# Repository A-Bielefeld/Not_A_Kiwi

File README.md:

# Not_A_Kiwi

This is an old begineer project, this electronics shouldn't be replicated or used for may reasons. It stands here as an archive to remind myself of how my very first project turned out!

Not A Kiwi is an Open-Source, fully 3D printed modular robot controlled by a custom PCB. Its aims are to be an educational platform for engineering students and an entry in the 2019 Coupe de France de Robotique for the Robotics Assocations of Télécom Physique Strasbourg as a secondary robot.

This robot is meant for anyone seeking to have a fun and looking for an open robotics plateform to learn and expand on. The only tool needed to build one is a 3D printer, as the PCB can be bought online or provided by me (soldered or not).

## Features
- Based on a standard ATMega32, the board is arduino compatible (tested).
- Many headers and an integrated breadboard to test out new ideas and add sensors.
- Very easy to print, no complex parts.
- Modular 3D printed structure makes it easy to add any kind of sensor or effector.
- ESP01 socket (UART or I2C communication with the AVR) for IoT applications.

## Hardware
The hardware is the most developped part of this project as the code is still being written.

### BOM
- 4 Nema17 stepper motors (38mm)
- 4 DRV8825 stepper motor driver carriers (or A4988-Pinout-Compatible)
- 5V Pololu Regulator (D24V5F5, but I intend to replace them with a simpler/cheaper solution)
- 3.3V Pololu regulator (D24V5F3)
- ESP01 (not required)
- 12V LiPo battery (but any 12V to 36V battery will work fine)
- Not A Kiwi Board (Detailed below)
- Small Breadboard
- 30mm 0.15A fan
- 3D printed structure

#### Not A Kiwi Board

The board is a simple Atmega32 based board that includes 4 stepper motor driver carriers sockets as well as support for an ESP01 chip, communicating over either UART or I2C depending on a choice of jumpers. The BOM is rather small, as the board is meant to be programmed through ICSP. It is easily possible to send the BOM and Gerber files to a PCB production service to obtain one, although I can also provide fully soldered and tested ones for a fee (Europe only).

#### PCB BOM
The board uses a majority of SMD components, all 1206 except the AVR smoothing capacitor and a zener diode.

Most of these components can be soldered by hand, although it is advised to use solder paste and a reflow oven (a simple and inexpensive toaster oven is enough for this purpose).

Full BOM files will be provided in the repository, in a format compatible with most PCB manufacturers. 
An article explaining the choices behind the parts, and possible alternatives will be available on the wiki.

#### 3D printed structure

  The robot uses a simple 3D printed structure composed of 12 parts, it takes approximately 12 hours to print, not counting in the 3D printed omniwheels, but it would be much better to use bought ones, albeit more expensive (3D printed wheels have a negligeable cost, but perform more poorly, several design will be tested and offered here).
  
  The CAD files provided are Fusion 360 parametric files and therefore should also be compatible with Autodesk Inventor and SolidWorks (tested). If you just wish to print the robot, .STL files are also provided. The Kit also uses M3 screws and nuts, it is very quick and easy to assemble (less than an hour).

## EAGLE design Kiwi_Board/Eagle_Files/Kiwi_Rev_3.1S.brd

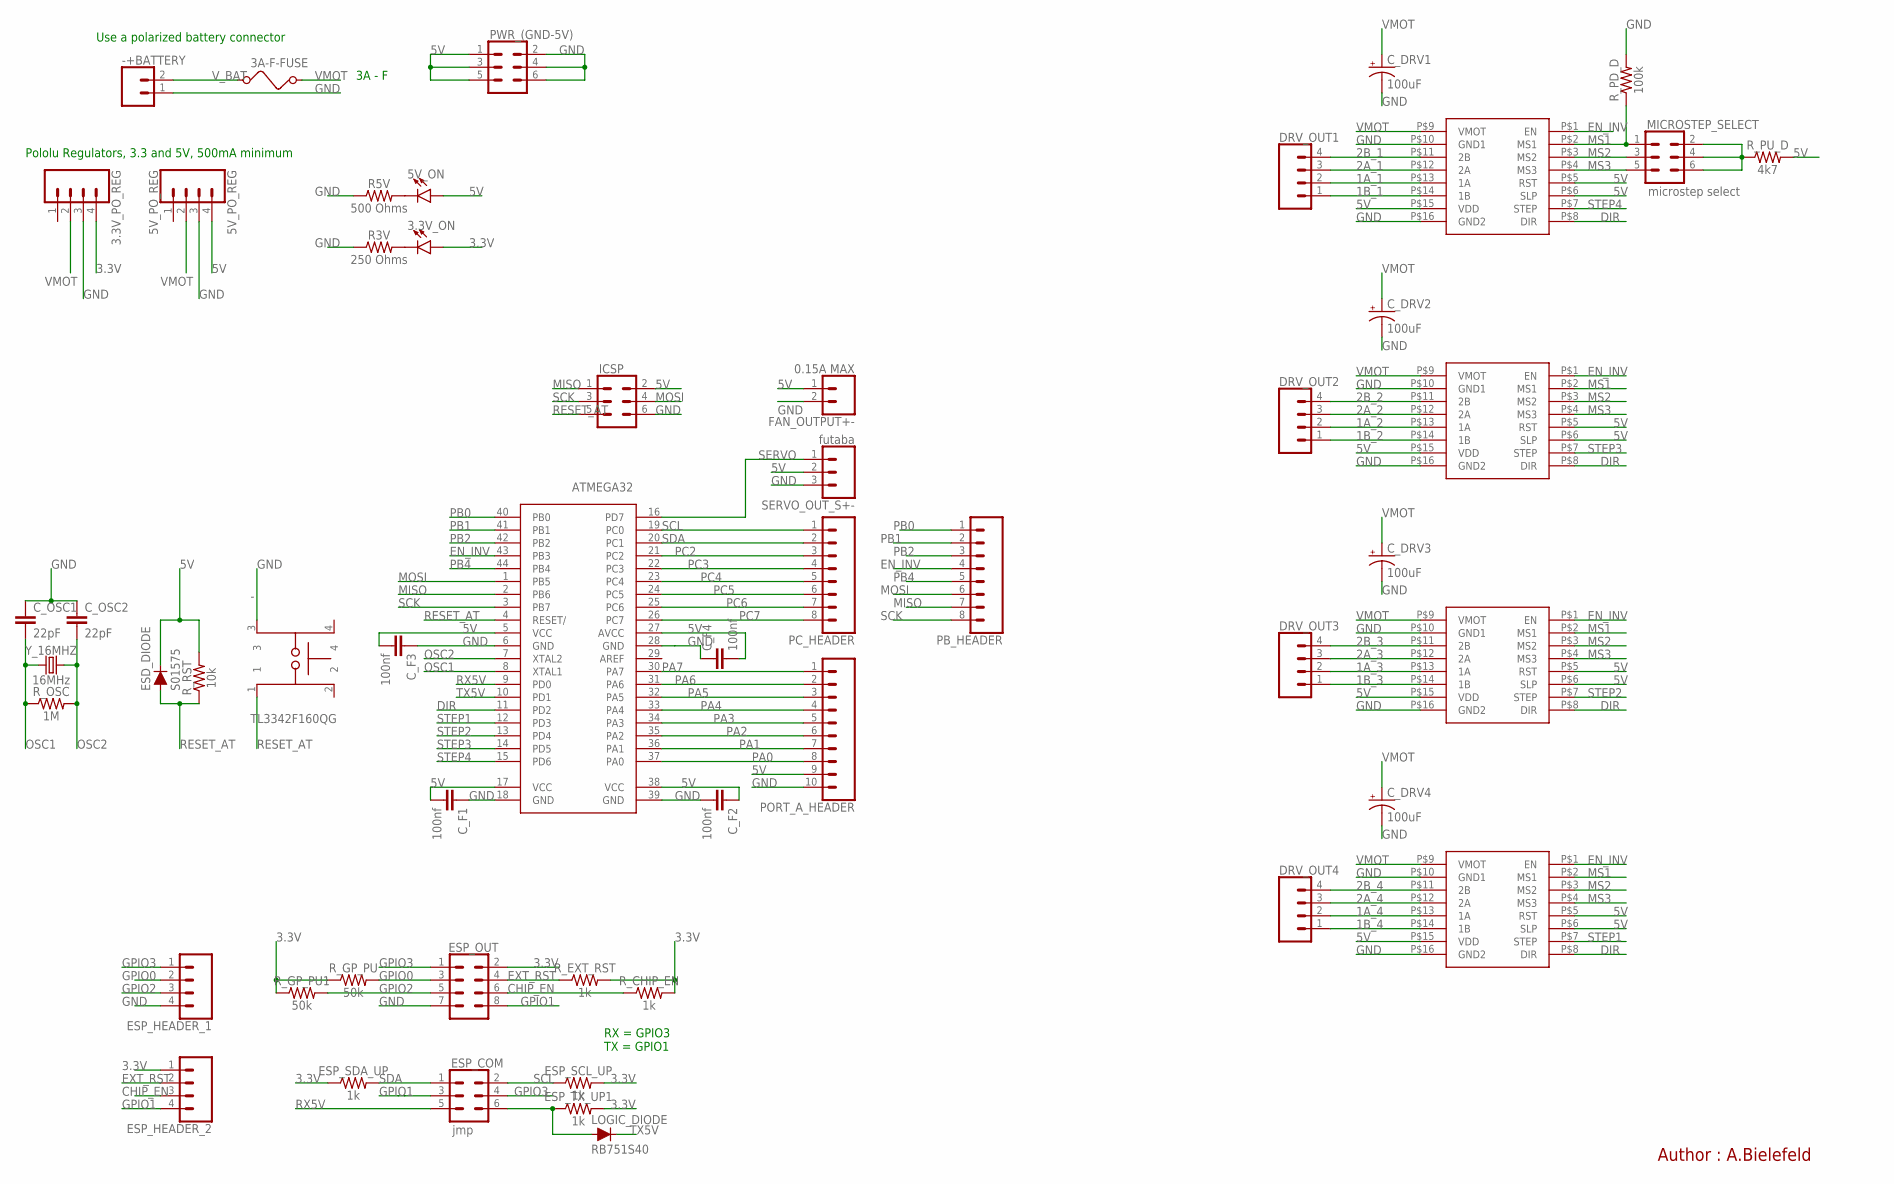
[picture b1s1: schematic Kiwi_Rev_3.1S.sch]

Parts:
3.3V_ON, 5V_ON: LED1206; LED-1206
3.3V_PO_REG: CONN_04; 1X04
3A-F-FUSE: FUSE
5V_PO_REG: 5V_PO_REG; 1X04
-: TL3342F160QG; SW_TL3342F160QG
-+BATTERY: CONN_023.5MM; SCREWTERMINAL-3.5MM-2
ATMEGA32: ATMEGA32; QFP80P1200X1200X120-44N
C_DRV1, C_DRV2, C_DRV3, C_DRV4: 100uF; CPOL-RADIAL-2.5MM-6.5MM
C_F1, C_F2, C_F3, C_F4: 100nf; 0603
C_OSC1, C_OSC2: 22pF; 1206
DRIVER1, DRIVER2, DRIVER3, DRIVER4: POLOLU_A4988; POLOLU_CARRIER
DRV_OUT1, DRV_OUT2, DRV_OUT3, DRV_OUT4: CONN_04; 1X04
ESD_DIODE: S01575; 1206
ESP_COM: jmp; 2X3
ESP_HEADER_1, ESP_HEADER_2: CONN_04; 1X04
ESP_OUT: CONN_04X2; 2X4
ESP_SCL_UP: 1k; 1206
ESP_SDA_UP: 1k; 1206
ESP_TX_UP1: 1k; 1206
FAN_OUTPUT+-: 0.15A MAX; 1X02
ICSP: CONN_03X22X3_SILK_MALE_PTH; 2X3
LOGIC_DIODE: RB751S40; SOD523
MICROSTEP_SELECT: microstep select; 2X3
PB_HEADER: CONN_08"; 1X08
PC_HEADER: CONN_08"; 1X08
PORT_A_HEADER: CONN_10"; 1X10
PWR_(GND-5V): CONN_03X22X3_SILK_MALE_PTH; 2X3
R3V: 250 Ohms; 1206
R5V: 500 Ohms; 1206
R_CHIP_EN: 1k; 1206
R_EXT_RST: 1k; 1206
R_GP_PU, R_GP_PU1: 50k; 1206
R_OSC: 1M; 1206
R_PD_D: 100k; 1206
R_PU_D: 4k7; 1206
R_RST: 10k; 1206
SERVO_OUT_S+-: futaba; 1X03
Y_16MHZ: 16MHz; HC49US

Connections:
1A_1: DRIVER1.P$13 (1A), DRV_OUT1.2
1A_2: DRIVER2.P$13 (1A), DRV_OUT2.2
1A_3: DRIVER3.P$13 (1A), DRV_OUT3.2
1A_4: DRIVER4.P$13 (1A), DRV_OUT4.2
1B_1: DRIVER1.P$14 (1B), DRV_OUT1.1
1B_2: DRIVER2.P$14 (1B), DRV_OUT2.1
1B_3: DRIVER3.P$14 (1B), DRV_OUT3.1
1B_4: DRIVER4.P$14 (1B), DRV_OUT4.1
2A_1: DRIVER1.P$12 (2A), DRV_OUT1.3
2A_2: DRIVER2.P$12 (2A), DRV_OUT2.3
2A_3: DRIVER3.P$12 (2A), DRV_OUT3.3
2A_4: DRIVER4.P$12 (2A), DRV_OUT4.3
2B_1: DRIVER1.P$11 (2B), DRV_OUT1.4
2B_2: DRIVER2.P$11 (2B), DRV_OUT2.4
2B_3: DRIVER3.P$11 (2B), DRV_OUT3.4
2B_4: DRIVER4.P$11 (2B), DRV_OUT4.4
3.3V: 3.3V_ON.A, 3.3V_PO_REG.4, ESP_HEADER_2.1, ESP_OUT.2, ESP_SCL_UP.2, ESP_SDA_UP.1, ESP_TX_UP1.2, R_CHIP_EN.2, R_EXT_RST.2, R_GP_PU.1, R_GP_PU1.1
5V: 5V_ON.A, 5V_PO_REG.4, ATMEGA32.5 (VCC), ATMEGA32.17 (VCC), ATMEGA32.27 (AVCC), ATMEGA32.38 (VCC), C_F1.2, C_F2.1, C_F3.2, C_F4.2, DRIVER1.P$5 (RST), DRIVER1.P$6 (SLP), DRIVER1.P$15 (VDD), DRIVER2.P$5 (RST), DRIVER2.P$6 (SLP), DRIVER2.P$15 (VDD), DRIVER3.P$5 (RST), DRIVER3.P$6 (SLP), DRIVER3.P$15 (VDD), DRIVER4.P$5 (RST), DRIVER4.P$6 (SLP), DRIVER4.P$15 (VDD), ESD_DIODE.2 (C), FAN_OUTPUT+-.1, ICSP.2, PORT_A_HEADER.9, PWR_(GND-5V).1, PWR_(GND-5V).3, PWR_(GND-5V).5, R_PU_D.2, R_RST.2, SERVO_OUT_S+-.2
CHIP_EN: ESP_HEADER_2.3, ESP_OUT.6, R_CHIP_EN.1
DIR: ATMEGA32.11 (PD2), DRIVER1.P$8 (DIR), DRIVER2.P$8 (DIR), DRIVER3.P$8 (DIR), DRIVER4.P$8 (DIR)
EN_INV: ATMEGA32.43 (PB3), DRIVER1.P$1 (EN), DRIVER2.P$1 (EN), DRIVER3.P$1 (EN), DRIVER4.P$1 (EN), PB_HEADER.4
EXT_RST: ESP_HEADER_2.2, ESP_OUT.4, R_EXT_RST.1
GND: 3.3V_PO_REG.3, 5V_PO_REG.3, -.3, -+BATTERY.1, ATMEGA32.6 (GND), ATMEGA32.18 (GND), ATMEGA32.28 (GND), ATMEGA32.39 (GND), C_DRV1.2 (-), C_DRV2.2 (-), C_DRV3.2 (-), C_DRV4.2 (-), C_F1.1, C_F2.2, C_F3.1, C_F4.1, C_OSC1.1, C_OSC2.1, DRIVER1.P$10 (GND1), DRIVER1.P$16 (GND2), DRIVER2.P$10 (GND1), DRIVER2.P$16 (GND2), DRIVER3.P$10 (GND1), DRIVER3.P$16 (GND2), DRIVER4.P$10 (GND1), DRIVER4.P$16 (GND2), ESP_HEADER_1.4, ESP_OUT.7, FAN_OUTPUT+-.2, ICSP.6, PORT_A_HEADER.10, PWR_(GND-5V).2, PWR_(GND-5V).4, PWR_(GND-5V).6, R3V.1, R5V.1, R_PD_D.2, SERVO_OUT_S+-.3
GPIO0: ESP_HEADER_1.2, ESP_OUT.3, R_GP_PU.2
GPIO1: ESP_COM.3, ESP_HEADER_2.4, ESP_OUT.8
GPIO2: ESP_HEADER_1.3, ESP_OUT.5, R_GP_PU1.2
GPIO3: ESP_COM.4, ESP_HEADER_1.1, ESP_OUT.1
MISO: ATMEGA32.2 (PB6), ICSP.1, PB_HEADER.7
MOSI: ATMEGA32.1 (PB5), ICSP.4, PB_HEADER.6
MS1: DRIVER1.P$2 (MS1), DRIVER2.P$2 (MS1), DRIVER3.P$2 (MS1), DRIVER4.P$2 (MS1), MICROSTEP_SELECT.1, R_PD_D.1
MS2: DRIVER1.P$3 (MS2), DRIVER2.P$3 (MS2), DRIVER3.P$3 (MS2), DRIVER4.P$3 (MS2), MICROSTEP_SELECT.3
MS3: DRIVER1.P$4 (MS3), DRIVER2.P$4 (MS3), DRIVER3.P$4 (MS3), DRIVER4.P$4 (MS3), MICROSTEP_SELECT.5
unnamed: 3.3V_ON.C, R3V.2
unnamed: 5V_ON.C, R5V.2
unnamed: ESP_COM.6, ESP_TX_UP1.1, LOGIC_DIODE.A
NET_PU1: MICROSTEP_SELECT.2, MICROSTEP_SELECT.4, MICROSTEP_SELECT.6, R_PU_D.1
OSC1: ATMEGA32.8 (XTAL1), C_OSC1.2, R_OSC.1, Y_16MHZ.1
OSC2: ATMEGA32.7 (XTAL2), C_OSC2.2, R_OSC.2, Y_16MHZ.2
PA0: ATMEGA32.37 (PA0), PORT_A_HEADER.8
PA1: ATMEGA32.36 (PA1), PORT_A_HEADER.7
PA2: ATMEGA32.35 (PA2), PORT_A_HEADER.6
PA3: ATMEGA32.34 (PA3), PORT_A_HEADER.5
PA4: ATMEGA32.33 (PA4), PORT_A_HEADER.4
PA5: ATMEGA32.32 (PA5), PORT_A_HEADER.3
PA6: ATMEGA32.31 (PA6), PORT_A_HEADER.2
PA7: ATMEGA32.30 (PA7), PORT_A_HEADER.1
PB0: ATMEGA32.40 (PB0), PB_HEADER.1
PB1: ATMEGA32.41 (PB1), PB_HEADER.2
PB2: ATMEGA32.42 (PB2), PB_HEADER.3
PB4: ATMEGA32.44 (PB4), PB_HEADER.5
PC2: ATMEGA32.21 (PC2), PC_HEADER.3
PC3: ATMEGA32.22 (PC3), PC_HEADER.4
PC4: ATMEGA32.23 (PC4), PC_HEADER.5
PC5: ATMEGA32.24 (PC5), PC_HEADER.6
PC6: ATMEGA32.25 (PC6), PC_HEADER.7
PC7: ATMEGA32.26 (PC7), PC_HEADER.8
RESET_AT: -.1, ATMEGA32.4 (RESET/), ESD_DIODE.1 (A), ICSP.5, R_RST.1
RX5V: ATMEGA32.9 (PD0), ESP_COM.5
SCK: ATMEGA32.3 (PB7), ICSP.3, PB_HEADER.8
SCL: ATMEGA32.19 (PC0), ESP_COM.2, ESP_SCL_UP.1, PC_HEADER.1
SDA: ATMEGA32.20 (PC1), ESP_COM.1, ESP_SDA_UP.2, PC_HEADER.2
SERVO: ATMEGA32.16 (PD7), SERVO_OUT_S+-.1
STEP1: ATMEGA32.12 (PD3), DRIVER4.P$7 (STEP)
STEP2: ATMEGA32.13 (PD4), DRIVER3.P$7 (STEP)
STEP3: ATMEGA32.14 (PD5), DRIVER2.P$7 (STEP)
STEP4: ATMEGA32.15 (PD6), DRIVER1.P$7 (STEP)
TX5V: ATMEGA32.10 (PD1), LOGIC_DIODE.C
VMOT: 3.3V_PO_REG.2, 3A-F-FUSE.2, 5V_PO_REG.2, C_DRV1.1 (+), C_DRV2.1 (+), C_DRV3.1 (+), C_DRV4.1 (+), DRIVER1.P$9 (VMOT), DRIVER2.P$9 (VMOT), DRIVER3.P$9 (VMOT), DRIVER4.P$9 (VMOT)
V_BAT: 3A-F-FUSE.1, -+BATTERY.2

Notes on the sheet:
Use a polarized battery connector
3A - F
RX = GPIO3 TX = GPIO1
Pololu Regulators, 3.3 and 5V, 500mA minimum
Author : A.Bielefeld

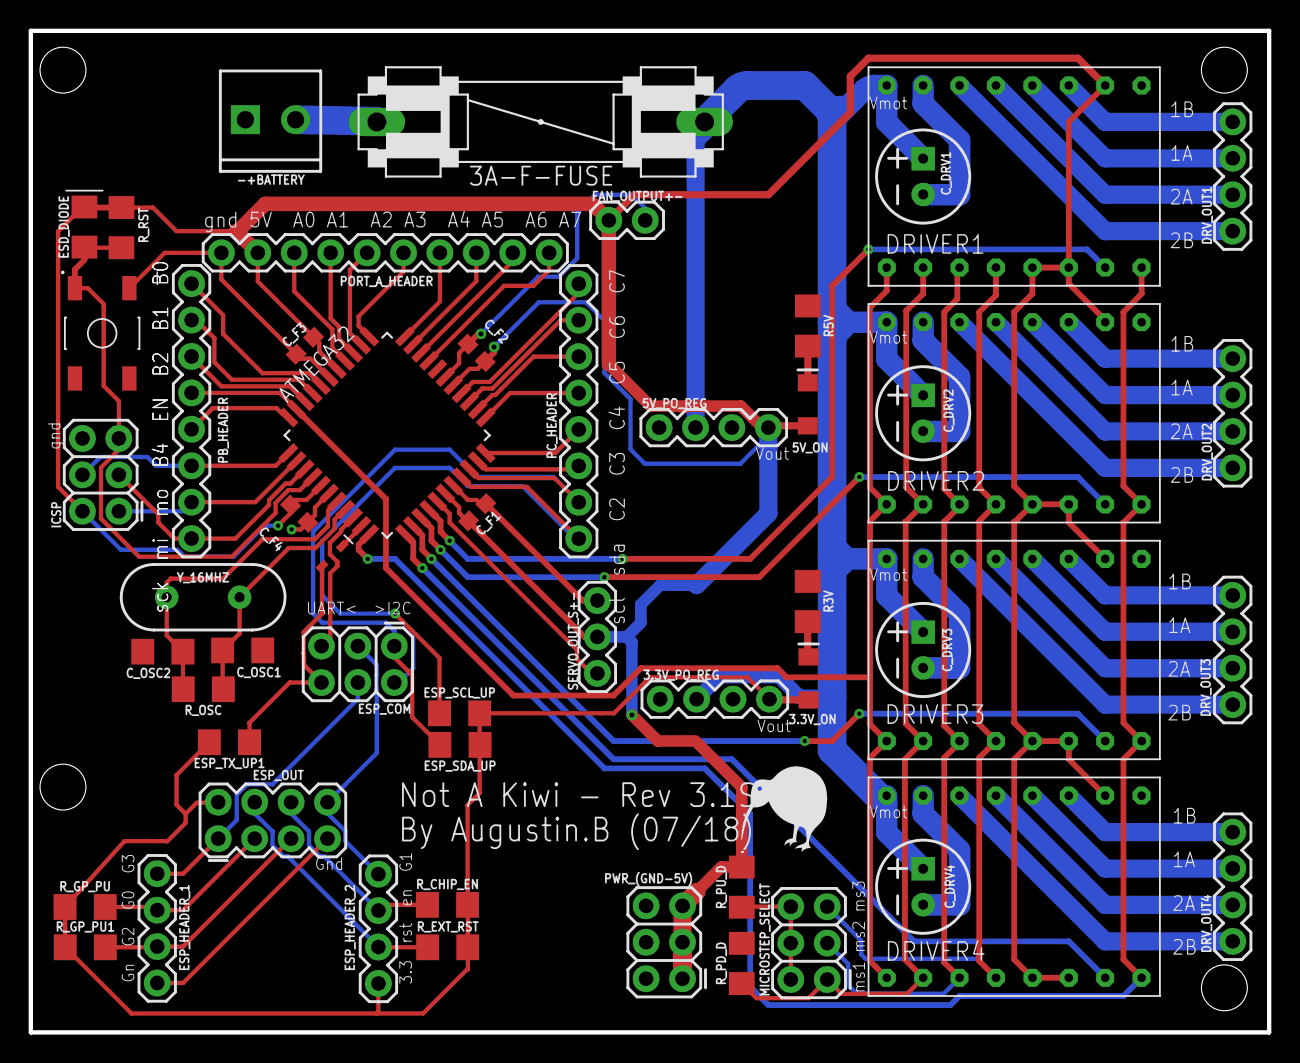
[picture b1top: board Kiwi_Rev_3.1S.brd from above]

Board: 2 copper layers, 86.4 x 69.8 mm, 54 parts (0 on the bottom side), 69 nets.

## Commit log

2018-08-28 Small suggestions for a slightly cleaner README
2018-11-01 Uploaded pictures for readme
2018-11-01 added logos
2018-11-01 added pictures and several corrections to readme
2018-11-01 Added all the CAM and CAD files for the NAK Board
2019-01-11 added for archive purposes
2019-01-11 added new image for Two Wheeled Drive option
2019-01-11 Added driver code for two wheeled driving mode
    Simple polar movements without accelerations are supported, rotate, linear moves, and simple movement logic and laying out work for an acceleration class, as well as future use of the bresenham algor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
2019-01-11 added readme
2019-01-13 small readme update
2019-01-30 Non working accelerationg ramp generation code for differencial drive

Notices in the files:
parts and their libraries:
SparkFun-Connectors: Licensing: Creative Commons ShareAlike 4.0 International - https://creativecommons.org/licenses/by-sa/4.0
